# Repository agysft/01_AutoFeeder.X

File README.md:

# AutoFeeder

This is a test project for an auto-feeder for CompactPnP. When the switch is pressed, the feeder moves one frame. It includes a program and a schematic. The program was written in PIC MPLAB X IDE. The schematic is written in KiCAD and the printed circuit board is made. The structure was made with a 3D printer.

---
これはCompactPnP用のオートフィーダーのテスト用プロジェクトです。スイッチが押されるとフィーダーが一コマ移動します。プログラムと回路図を含みます。プログラムはPIC MPLAB X IDEで書きました。回路図はKiCADで書き、プリント基板を作っています。構造物は3Dプリンターで作りました。

---
### Rev.01
* [demo](image/ezgif.com-video-to-gif-converted.gif)
* [schematics](schematics/AutoFeeder_Drum-type_new/20231123_R1/AutoFeeder_Drum-type.pdf) 
* block chart
```mermaid
graph LR
  A[Timer2]-->B[PWM3]-->C
  subgraph BA6211
  C[FWD]
  E[REV]
  end
  A-->D[PWM4]-->E
  F[Sensor0]-->|-|M[CMP2]-->N[LED Green]
    L[FVR 1.024V]-->|+|M
    L-->|+|Q
  I[Sensor1]-->|-|Q[CMP1]-->K[LED Red]
```
---

### Rev.02
フォトセンサーの感度を切り替える回路と、ドラムの角度を取得するためのAS5600という磁気センサーと、I2CのLCDを接続できるようにしました。Add a circuit to switch the sensitivity of the photo sensor, a magnetic sensor named AS5600 to get the angle of the drum, and the LCD.

* [demo](image/20240212_AutoFeederTest-ezgif.com-video-to-gif-converter.gif)
* [schematics](schematics/AutoFeeder_Drum-type_new/20240107_Rev02/AutoFeeder_Drum-type.pdf) 
* block chart

```mermaid
graph LR
  G[Senror1 Radder detector]--> S
  F[Sensor0 Tape-hole detector]--> S
  S{Switch} -->| M- |M
  subgraph BA6211
  C[FWD]
  E[REV]
  end
  BA6211 --- Z[Motor]
  subgraph PIC16F1705
  A[Timer2 50KHz]-->D
  A-->B
  B[PWM3 -- RC5]---C
  D[PWM4 -- RC4]---E
  L[FVR 2.048V]-->| P+ |M[CMP2 -- RA0]
  RA4[GPIO RA4 Open Drain]
  RA5[GPIO RA5 Open Drain]
  end
  M-->N[LED]
  AS5600---|I2C|PIC16F1705
  PIC16F1705---|I2C|LCD
  
  H[Optical Sensor Sensitivity Selector]---RA4
  H---RA5
```

* High-Endurance Flash memory (HEF) usage 0x1F80-0x1F9F
  | Offset Address | note (1 word = 14-bit wide) |
  |:--:|---- 
  | 25 .. 31 | No Use |
  | 2 .. 24 | Tape hole position data (12-bit wide) |
  | 1 | Tape-Color data (White/Transparent/Black)|
  | 0 | AS5600 Magnetic data of origin (12-bit wide) |
* HEF 0x1FA0-0x1FFF is not use.

---
### AutoFeeder2 Rev.1
Autofeeder Rev.02の機能はそのままに、基板を縦置きする事で省スペース化を図りました。また、透過型のフォトインタラプターCNZ1023を使えるようにしました。The functions of the Autofeeder are retained, but the board is placed vertically to save space. Transmissive photo interrupter CNZ1023 can also be used.

* [demo](image/20240803_AutoFeeder_Test2.gif)
* [schematics](schematics/AutoFeeder_Drum-type_2/20240519_AF2_rev1/AutoFeeder_Drum-type.pdf) 

---
### Tips

* PIC16F1705でI2C を設定する。何故か400kHzに設定するとハングします。「Registers」で SSP1ADD = 0x9 (=400KHz)に設定することは可能。
  
  Setting I2C on the PIC16F1705. It hangs when set to 400kHz. It is possible to set SSP1ADD = 0x9 (=400KHz) in "Registers".

* このI2Cのサンプルコードがよく出来ていてそのままincludeして使える。
  This I2C sample code is well done and can be included and used as is.

* HEF-block範囲にプログラムが書かれないようにする設定。
  Settings to prevent programs from being written in the HEF-block range

* PICに書いた時にHEFブロックが初期化されない設定。
  Settings to prevent the HEF-block from being initialized when writing to the PIC

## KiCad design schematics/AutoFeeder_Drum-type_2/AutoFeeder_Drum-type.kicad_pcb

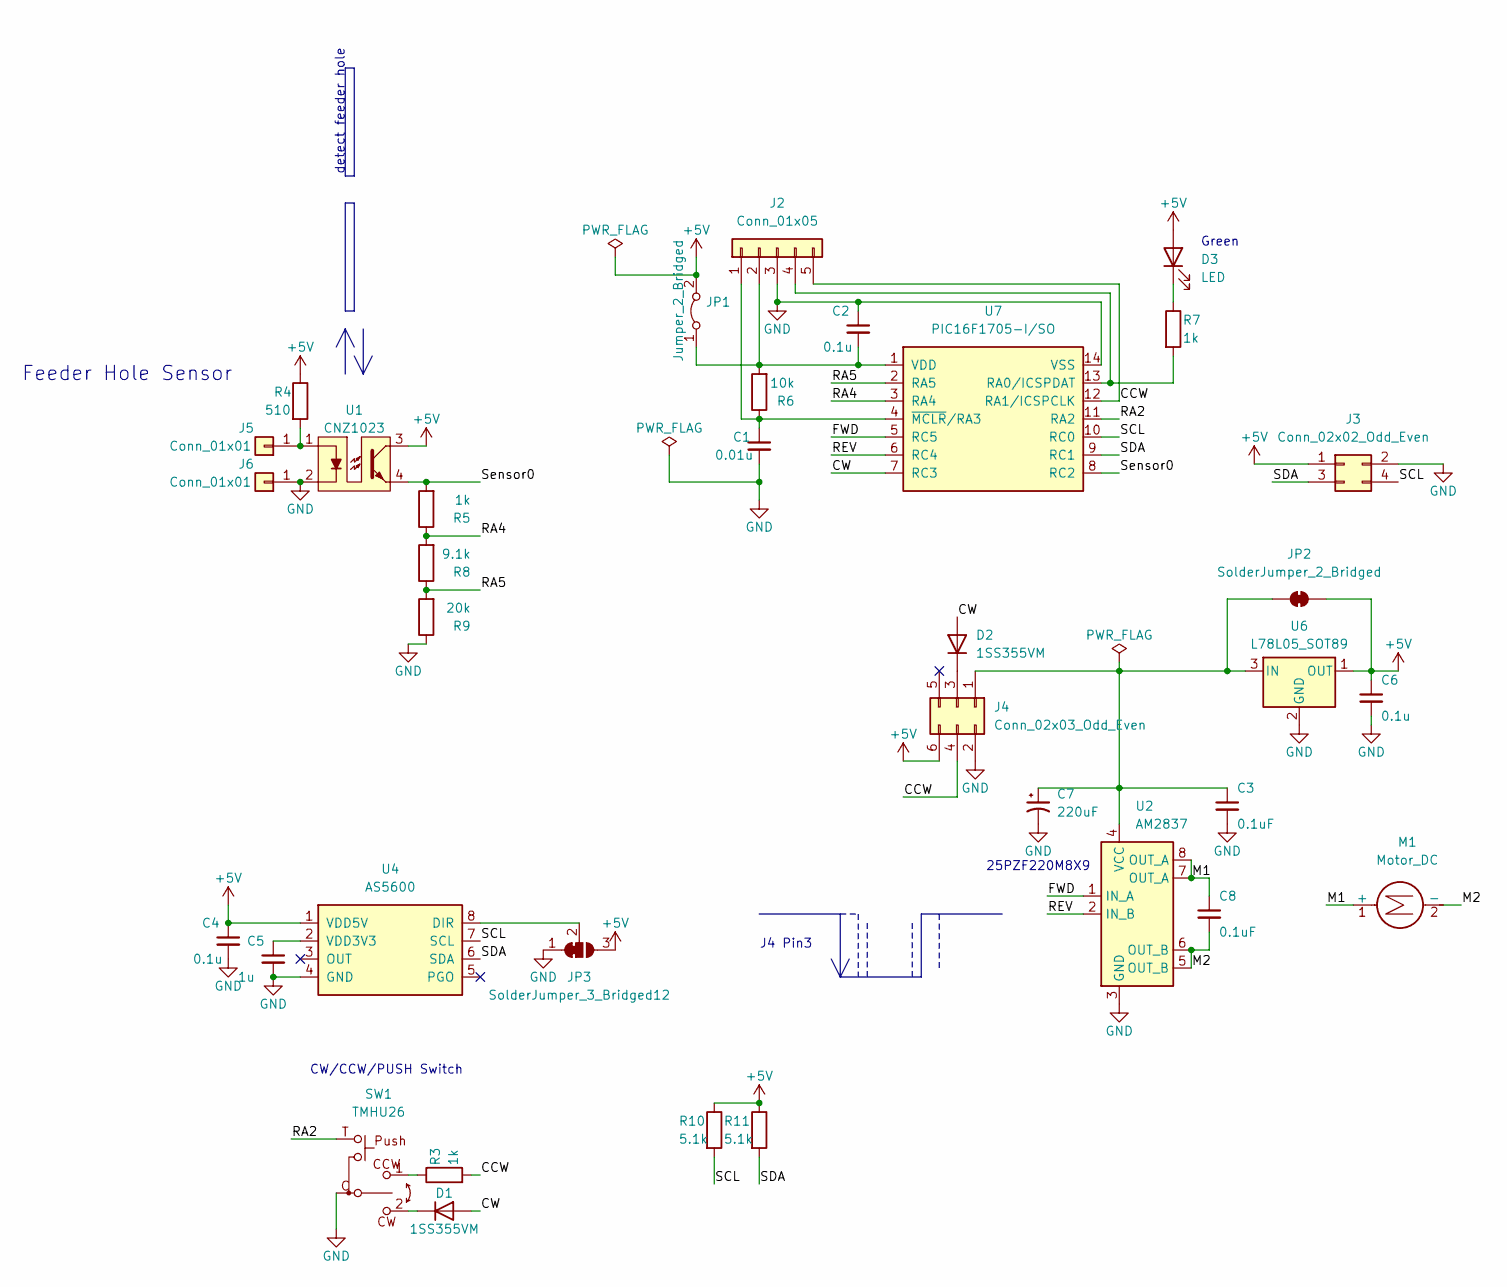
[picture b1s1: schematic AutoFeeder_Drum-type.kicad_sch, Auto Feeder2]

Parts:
C1: 0.01u; C_0603_1608Metric
C2, C4, C6: 0.1u; C_0805_2012Metric
C3, C8: 0.1uF; C_0805_2012Metric
C5: 1u; C_0805_2012Metric
C7: 220uF; CP_Radial_D8.0mm_P3.50mm
D1, D2: 1SS355VM; D_SOD-323F
D3: LED; LED_0603_1608Metric
J2: Conn_01x05; PinHeader_1x05_P2.54mm_Vertical
J3: Conn_02x02_Odd_Even; PinHeader_2x02_P2.54mm_Vertical
J4: Conn_02x03_Odd_Even; PinHeader_2x03_P2.54mm_Vertical
J5, J6: Conn_01x01; PinHeader_1x01_P2.54mm_Vertical
JP1: Jumper_2_Bridged; PinHeader_1x02_P2.54mm_Horizontal
JP2: SolderJumper_2_Bridged; SolderJumper-2_P1.3mm_Bridged_RoundedPad1.0x1.5mm
JP3: SolderJumper_3_Bridged12; SolderJumper-3_P1.3mm_Bridged12_RoundedPad1.0x1.5mm
M1: Motor_DC; JST_XH_B2B-XH-A_1x02_P2.50mm_Vertical
R3, R5, R7: 1k; R_0603_1608Metric
R4: 510; R_0603_1608Metric
R6: 10k; R_0603_1608Metric
R8: 9.1k; R_0603_1608Metric
R9: 20k; R_0603_1608Metric
R10, R11: 5.1k; R_0603_1608Metric
SW1: TMHU26; THMU26_2
U1: CNZ1023
U2: AM2837; SOIC-8_3.9x4.9mm_P1.27mm
U4: AS5600; SOP-8_3.9x4.9mm_P1.27mm
U6: L78L05_SOT89; SOT-89-3
U7: PIC16F1705-I/SO; SOIC-14_3.9x8.7mm_P1.27mm

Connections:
+5V: C4.1, C6.1, D3.2 (A), J3.1, J4.6, JP1.2 (B), JP2.2 (B), JP3.3 (B), R4.1, R10.1, R11.1, U1.3, U4.1 (VDD5V), U6.1 (OUT)
/CCW: J2.5, J4.4, R3.2, U7.12 (RA1/ICSPCLK)
/CW: D1.2 (A), D2.2 (A), U7.7 (RC3)
/FWD: U2.1 (IN_A), U7.5 (RC5)
/M1: C8.1, M1.1 (+), U2.7 (OUT_A), U2.8 (OUT_A)
/M2: C8.2, M1.2 (-), U2.5 (OUT_B), U2.6 (OUT_B)
/RA2: SW1.T, U7.11 (RA2)
/RA4: R5.1, R8.2, U7.3 (RA4)
/RA5: R8.1, R9.2, U7.2 (RA5)
/REV: U2.2 (IN_B), U7.6 (RC4)
/SCL: J3.4, R10.2, U4.7 (SCL), U7.10 (RC0)
/SDA: J3.3, R11.2, U4.6 (SDA), U7.9 (RC1)
/Sensor0: R5.2, U1.4, U7.8 (RC2)
GND: C1.2, C2.1, C3.2, C4.2, C5.2, C6.2, C7.2, J2.3, J3.2, J4.2, J6.1, JP3.1 (A), R9.1, SW1.C, U1.2, U2.3 (GND), U4.4 (GND), U6.2 (GND), U7.14 (VSS)
unnamed: D1.1 (K), SW1.2
unnamed: D2.1 (K), J4.3
unnamed: D3.1 (K), R7.1
unnamed: C1.1, J2.1, R6.1, U7.4 (~MCLR/RA3)
unnamed: C2.2, J2.2, JP1.1 (A), R6.2, U7.1 (VDD)
unnamed: J2.4, R7.2, U7.13 (RA0/ICSPDAT)
unnamed: C3.1, C7.1, J4.1, JP2.1 (A), U2.4 (VCC), U6.3 (IN)
unnamed: J5.1, R4.2, U1.1
unnamed: JP3.2 (C), U4.8 (DIR)
unnamed: R3.1, SW1.1
unnamed: C5.1, U4.2 (VDD3V3)

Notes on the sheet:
J4 Pin3
Green
detect feeder hole
CW/CCW/PUSH Switch
Feeder Hole Sensor
25PZF220M8X9

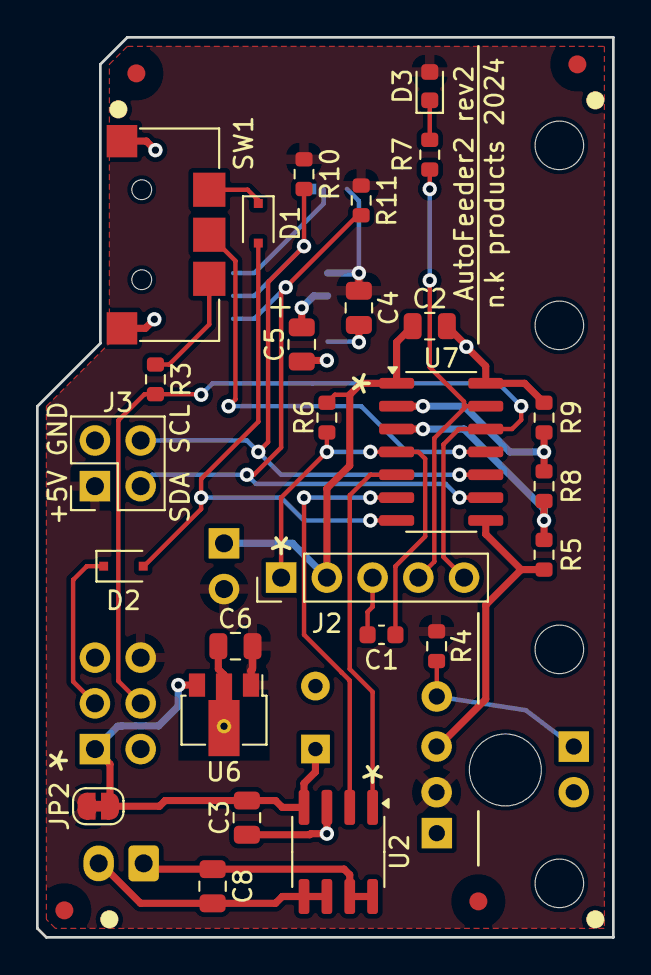
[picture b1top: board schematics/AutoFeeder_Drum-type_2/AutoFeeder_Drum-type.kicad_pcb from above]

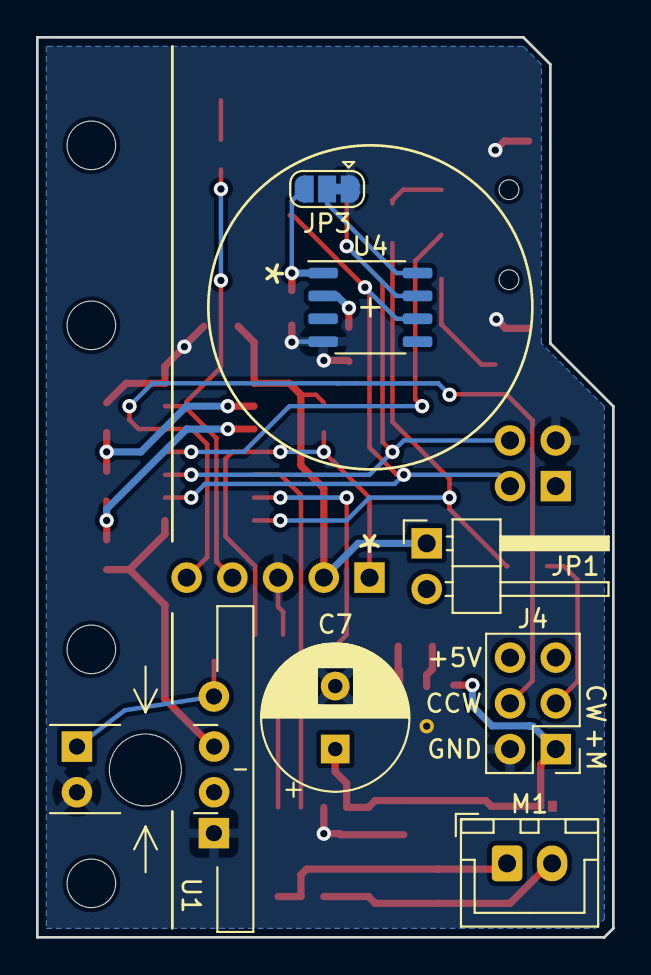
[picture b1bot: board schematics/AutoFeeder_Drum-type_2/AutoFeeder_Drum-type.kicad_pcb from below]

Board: 2 copper layers, 32.0 x 50.0 mm, 43 parts (9 on the bottom side), 25 nets.

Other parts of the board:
Fed1, Fed2, Fed3: Fiducial_1mm_Mask3mm
Fid4: Fiducial_1mm_Mask3mm
Fid5, Fid6, Fid7, Fid8: Fiducial_Silk

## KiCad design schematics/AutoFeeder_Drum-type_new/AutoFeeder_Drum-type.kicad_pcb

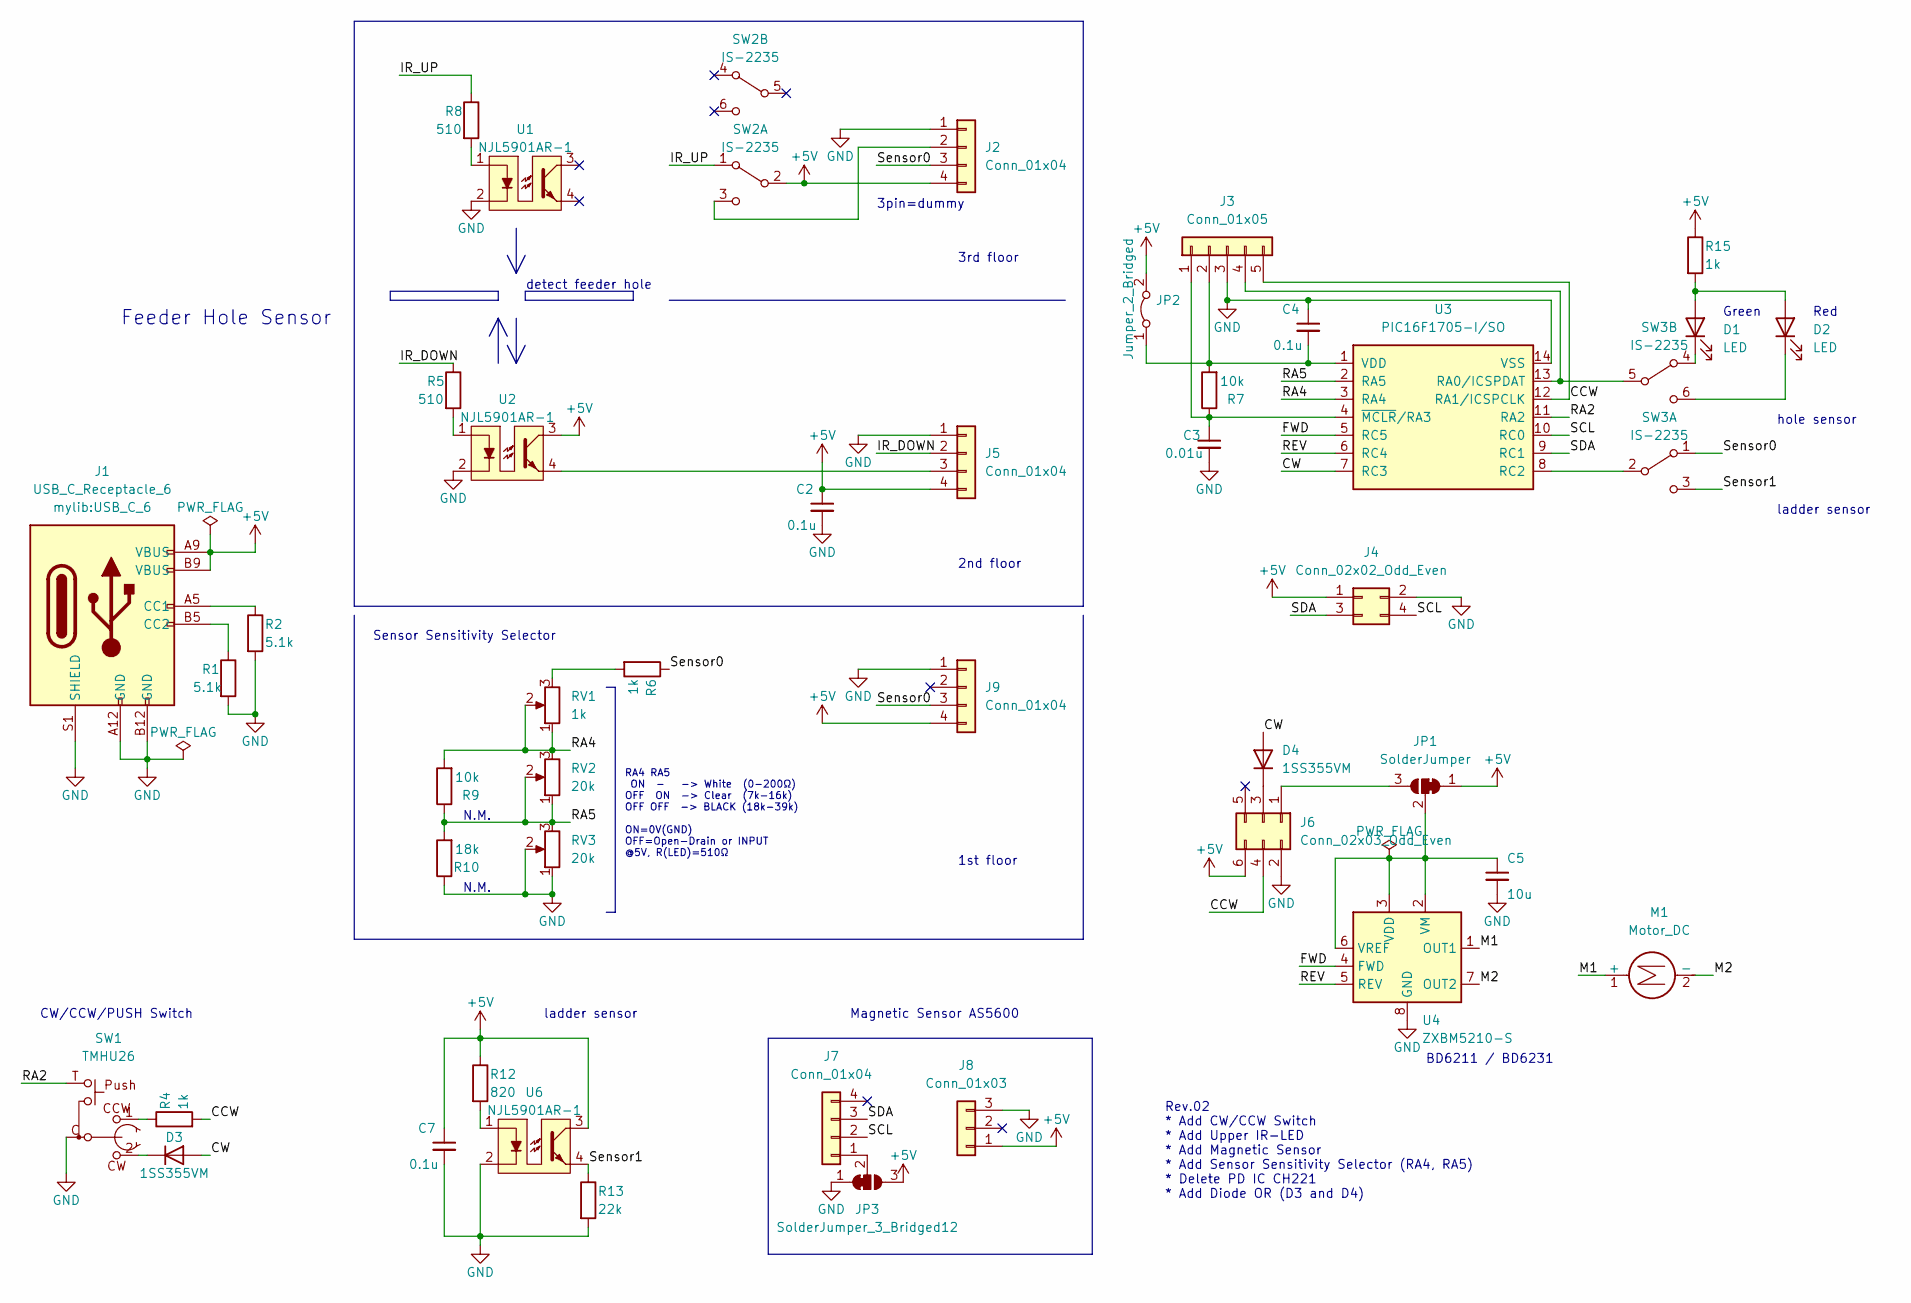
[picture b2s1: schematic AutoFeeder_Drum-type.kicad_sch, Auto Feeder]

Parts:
C2, C4, C7: 0.1u; C_0603_1608Metric
C3: 0.01u; C_0603_1608Metric
C5: 10u; C_0805_2012Metric
D1, D2: LED; LED_0603_1608Metric
D3, D4: 1SS355VM; D_SOD-323F
J1: USB_C_Receptacle_6; USB_C_6
J2, J5, J7, J9: Conn_01x04; PinHeader_1x04_P2.54mm_Vertical
J3: Conn_01x05; PinHeader_1x05_P2.54mm_Vertical
J4: Conn_02x02_Odd_Even; PinHeader_2x02_P2.54mm_Vertical
J6: Conn_02x03_Odd_Even; PinHeader_2x03_P2.54mm_Vertical
J8: Conn_01x03; PinHeader_1x03_P2.54mm_Vertical
JP1: SolderJumper; SolderJumper-3_P1.3mm_Bridged12_RoundedPad1.0x1.5mm
JP2: Jumper_2_Bridged; PinHeader_2x01_P2.54mm_Vertical
JP3: SolderJumper_3_Bridged12; SolderJumper-3_P1.3mm_Bridged12_RoundedPad1.0x1.5mm
M1: Motor_DC; JST_XH_B2B-XH-A_1x02_P2.50mm_Vertical
R1, R2: 5.1k; R_0603_1608Metric
R4, R6, R15: 1k; R_0603_1608Metric
R5, R8: 510; R_0603_1608Metric
R7, R9: 10k; R_0603_1608Metric
R10: 18k; R_0603_1608Metric
R12: 820; R_0603_1608Metric
R13: 22k; R_0603_1608Metric
RV1: 1k; Potentiometer_Vishay_T73YP_Vertical
RV2, RV3: 20k; Potentiometer_Vishay_T73YP_Vertical
SW1: TMHU26; THMU26_2
SW2, SW3: IS-2235; Slide-SW-IS-2235
U1, U2, U6: NJL5901AR-1
U3: PIC16F1705-I/SO; SOIC-14_3.9x8.7mm_P1.27mm
U4: ZXBM5210-S; SOIC-8_3.9x4.9mm_P1.27mm

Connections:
+5V: C2.1, C7.1, J1.A9 (VBUS), J1.B9 (VBUS), J2.4, J4.1, J5.4, J6.6, J8.1, J9.4, JP1.1 (A), JP2.2 (B), JP3.3 (B), R12.1, R15.1, SW2.2 (B), U2.3, U6.3
/CCW: J3.5, J6.4, R4.2, U3.12 (RA1/ICSPCLK)
/CW: D3.2 (A), D4.2 (A), U3.7 (RC3)
/FWD: U3.5 (RC5), U4.4 (FWD)
/IR_DOWN: J5.2, R5.1
/IR_UP: R8.1, SW2.1 (A)
/M1: M1.1 (+), U4.1 (OUT1)
/M2: M1.2 (-), U4.7 (OUT2)
/RA2: SW1.T, U3.11 (RA2)
/RA4: R9.2, RV1.1, RV1.2, RV2.3, U3.3 (RA4)
/RA5: R9.1, R10.2, RV2.1, RV2.2, RV3.3, U3.2 (RA5)
/REV: U3.6 (RC4), U4.5 (REV)
/SCL: J4.4, J7.2, U3.10 (RC0)
/SDA: J4.3, J7.3, U3.9 (RC1)
/Sensor0: J2.3, J9.3, R6.1, SW3.1 (A)
/Sensor1: R13.1, SW3.3 (C), U6.4
GND: C2.2, C3.2, C4.1, C5.2, C7.2, J1.A12 (GND), J1.B12 (GND), J1.S1 (SHIELD), J2.1, J3.3, J4.2, J5.1, J6.2, J8.3, J9.1, JP3.1 (A), R1.2, R2.2, R10.1, R13.2, RV3.1, RV3.2, SW1.C, U1.2, U2.2, U3.14 (VSS), U4.8 (GND), U6.2
unnamed: C3.1, J3.1, R7.1, U3.4 (~MCLR/RA3)
unnamed: C4.2, J3.2, JP2.1 (A), R7.2, U3.1 (VDD)
unnamed: C5.1, JP1.2 (C), U4.2 (VM), U4.3 (VDD), U4.6 (VREF)
unnamed: D1.1 (K), SW3.4 (A)
unnamed: D1.2 (A), D2.2 (A), R15.2
unnamed: D2.1 (K), SW3.6 (C)
unnamed: D3.1 (K), SW1.2
unnamed: D4.1 (K), J6.3
unnamed: J1.A5 (CC1), R2.1
unnamed: J1.B5 (CC2), R1.1
unnamed: J2.2, SW2.3 (C)
unnamed: J3.4, SW3.5 (B), U3.13 (RA0/ICSPDAT)
unnamed: J5.3, U2.4
unnamed: J6.1, JP1.3 (B)
unnamed: J7.1, JP3.2 (C)
unnamed: R4.1, SW1.1
unnamed: R5.2, U2.1
unnamed: R6.2, RV1.3
unnamed: R8.2, U1.1
unnamed: R12.2, U6.1
unnamed: SW3.2 (B), U3.8 (RC2)

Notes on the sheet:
Green
detect feeder hole
1st floor
RA4 RA5 ON - -> White (0-200Ω) OFF ON -> Clear (7k-16k) OFF OFF -> BLACK (18k-39k) ON=0V(GND) OFF=Open-Drain or INPUT @5V, R(LED)=510Ω
3pin=dummy
BD6211 / BD6231
2nd floor
ladder sensor
Red
N.M.
CW/CCW/PUSH Switch
Feeder Hole Sensor
Magnetic Sensor AS5600
hole sensor
Rev.02 * Add CW/CCW Switch * Add Upper IR-LED * Add Magnetic Sensor * Add Sensor Sensitivity Selector (RA4, RA5) * Delete PD IC CH221 * Add Diode OR (D3 and D4)
Sensor Sensitivity Selector
3rd floor

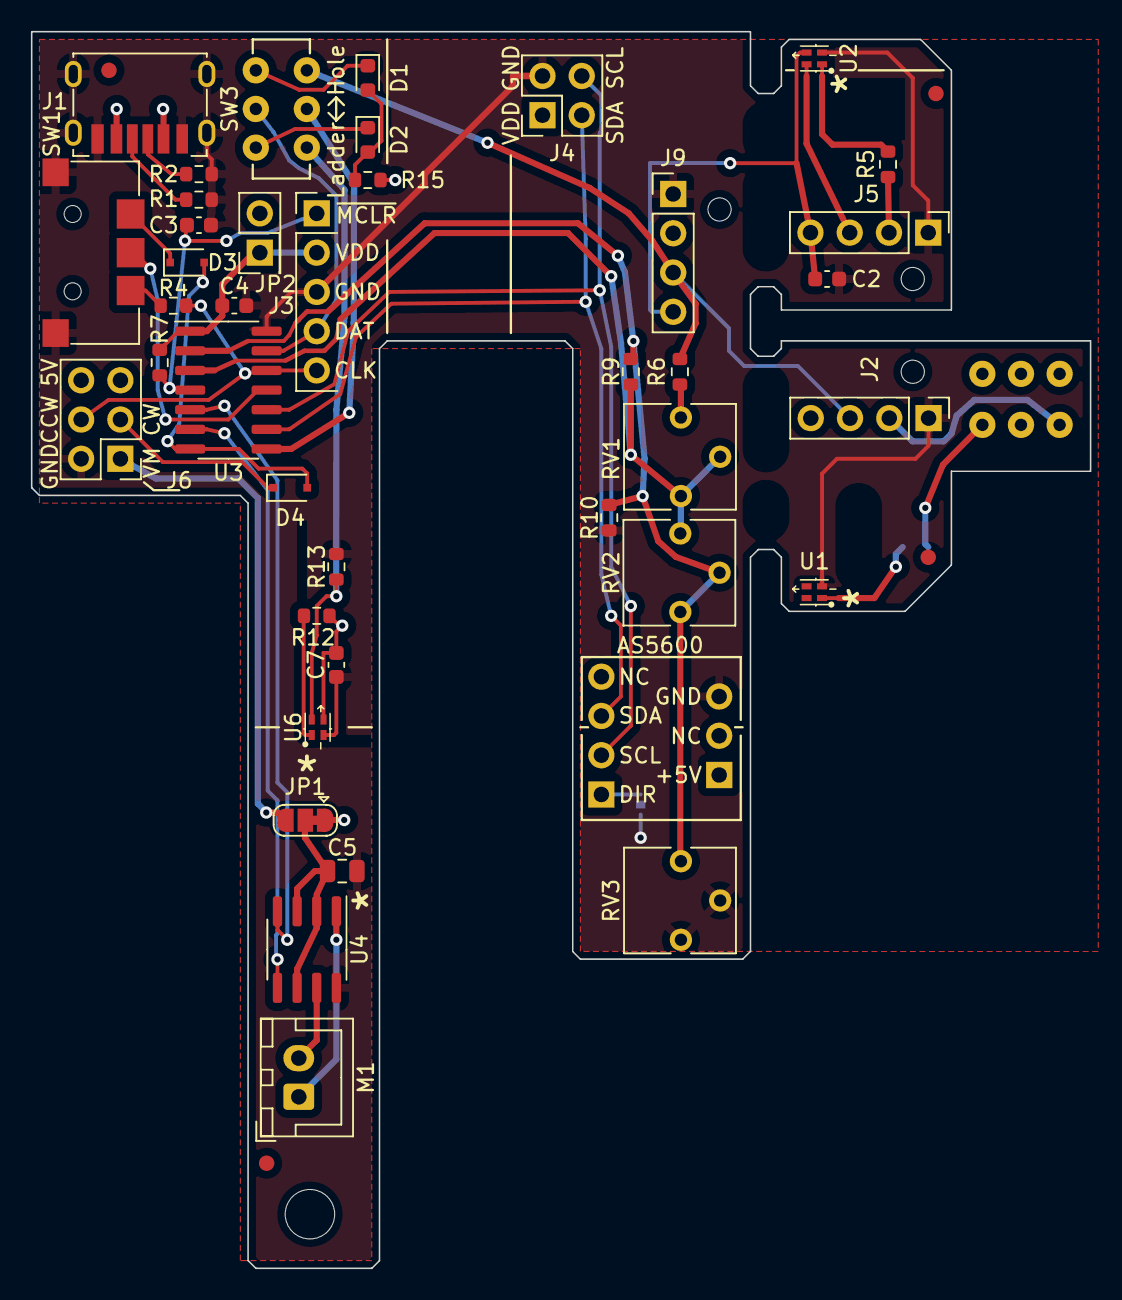
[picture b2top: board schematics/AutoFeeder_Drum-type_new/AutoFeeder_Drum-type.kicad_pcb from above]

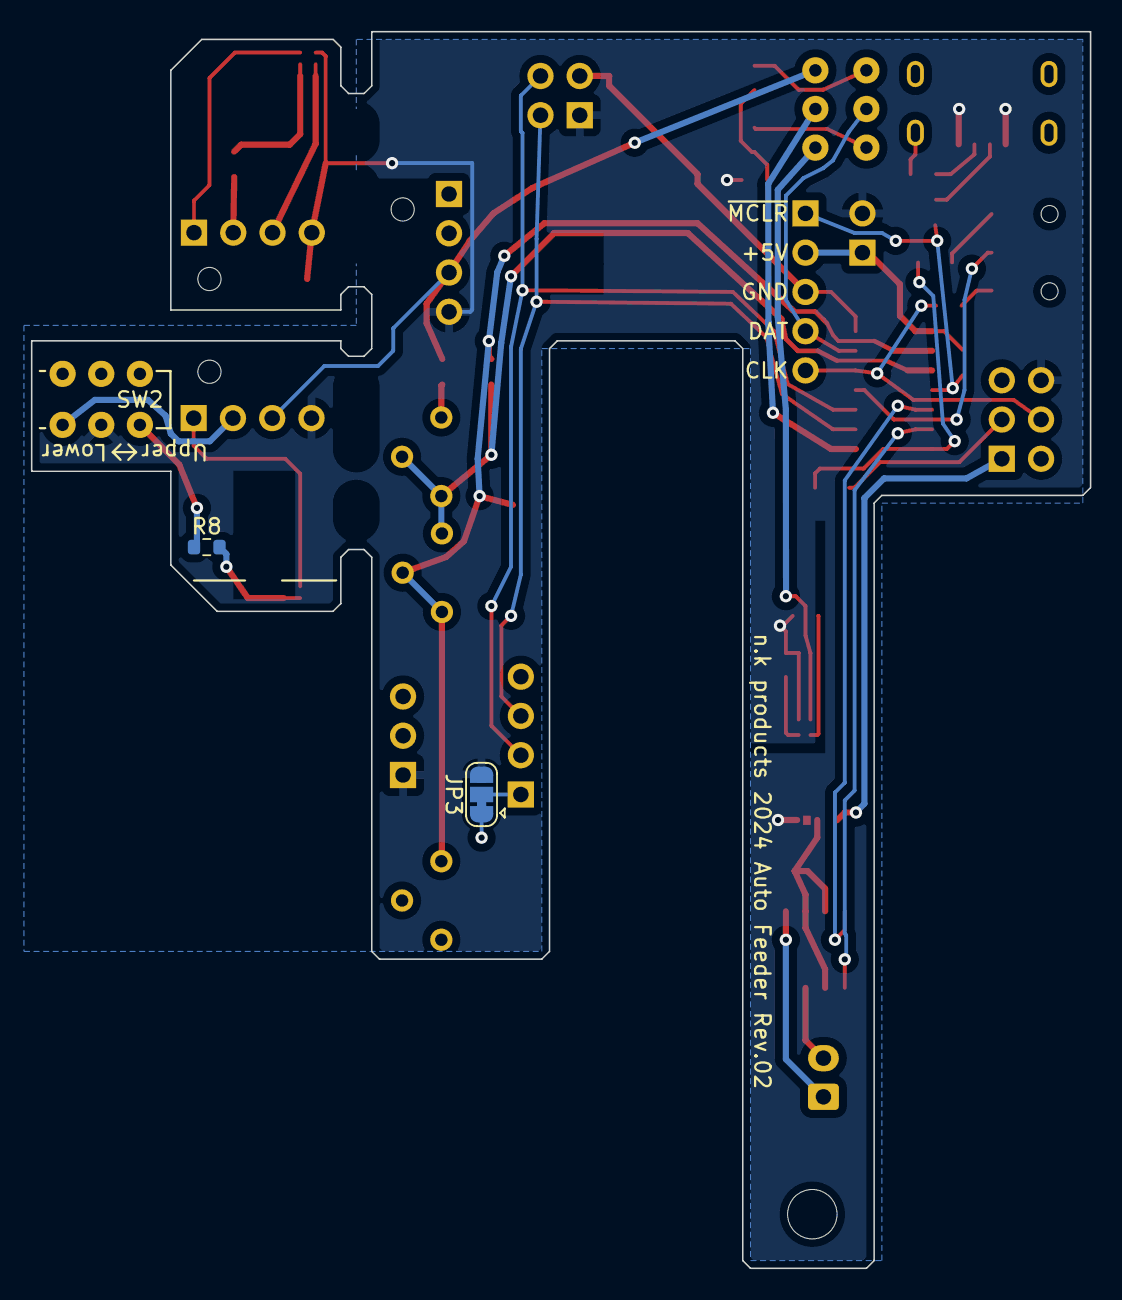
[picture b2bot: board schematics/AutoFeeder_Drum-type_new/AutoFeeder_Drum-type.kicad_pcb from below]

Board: 2 copper layers, 68.5 x 80.0 mm, 45 parts (3 on the bottom side), 38 nets.

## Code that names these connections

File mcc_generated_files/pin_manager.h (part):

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#define RA0_SetHigh()            do { LATAbits.LATA0 = 1; } while(0)
#define RA0_SetLow()             do { LATAbits.LATA0 = 0; } while(0)
#define RA0_Toggle()             do { LATAbits.LATA0 = ~LATAbits.LATA0; } while(0)
#define RA0_GetValue()              PORTAbits.RA0
#define RA0_SetDigitalInput()    do { TRISAbits.TRISA0 = 1; } while(0)
#define RA0_SetDigitalOutput()   do { TRISAbits.TRISA0 = 0; } while(0)
#define RA0_SetPullup()             do { WPUAbits.WPUA0 = 1; } while(0)
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// get/set IO_RA1 aliases
#define IO_RA1_TRIS                 TRISAbits.TRISA1
#define IO_RA1_LAT                  LATAbits.LATA1
#define IO_RA1_PORT                 PORTAbits.RA1
#define IO_RA1_WPU                  WPUAbits.WPUA1
#define IO_RA1_OD                   ODCONAbits.ODA1
#define IO_RA1_ANS                  ANSELAbits.ANSA1
#define IO_RA1_SetHigh()            do { LATAbits.LATA1 = 1; } while(0)
#define IO_RA1_SetLow()             do { LATAbits.LATA1 = 0; } while(0)
#define IO_RA1_Toggle()             do { LATAbits.LATA1 = ~LATAbits.LATA1; } while(0)
#define IO_RA1_GetValue()           PORTAbits.RA1
#define IO_RA1_SetDigitalInput()    do { TRISAbits.TRISA1 = 1; } while(0)
#define IO_RA1_SetDigitalOutput()   do { TRISAbits.TRISA1 = 0; } while(0)
#define IO_RA1_SetPullup()          do { WPUAbits.WPUA1 = 1; } while(0)
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// get/set IO_RA2 aliases
#define IO_RA2_TRIS                 TRISAbits.TRISA2
#define IO_RA2_LAT                  LATAbits.LATA2
#define IO_RA2_PORT                 PORTAbits.RA2
#define IO_RA2_WPU                  WPUAbits.WPUA2
#define IO_RA2_OD                   ODCONAbits.ODA2
#define IO_RA2_ANS                  ANSELAbits.ANSA2
#define IO_RA2_SetHigh()            do { LATAbits.LATA2 = 1; } while(0)
#define IO_RA2_SetLow()             do { LATAbits.LATA2 = 0; } while(0)
#define IO_RA2_Toggle()             do { LATAbits.LATA2 = ~LATAbits.LATA2; } while(0)
#define IO_RA2_GetValue()           PORTAbits.RA2
#define IO_RA2_SetDigitalInput()    do { TRISAbits.TRISA2 = 1; } while(0)
#define IO_RA2_SetDigitalOutput()   do { TRISAbits.TRISA2 = 0; } while(0)
#define IO_RA2_SetPullup()          do { WPUAbits.WPUA2 = 1; } while(0)
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// get/set IO_RA4 aliases
#define IO_RA4_TRIS                 TRISAbits.TRISA4
#define IO_RA4_LAT                  LATAbits.LATA4
#define IO_RA4_PORT                 PORTAbits.RA4
#define IO_RA4_WPU                  WPUAbits.WPUA4
#define IO_RA4_OD                   ODCONAbits.ODA4
#define IO_RA4_ANS                  ANSELAbits.ANSA4
#define IO_RA4_SetHigh()            do { LATAbits.LATA4 = 1; } while(0)
#define IO_RA4_SetLow()             do { LATAbits.LATA4 = 0; } while(0)
#define IO_RA4_Toggle()             do { LATAbits.LATA4 = ~LATAbits.LATA4; } while(0)
#define IO_RA4_GetValue()           PORTAbits.RA4
#define IO_RA4_SetDigitalInput()    do { TRISAbits.TRISA4 = 1; } while(0)
#define IO_RA4_SetDigitalOutput()   do { TRISAbits.TRISA4 = 0; } while(0)
#define IO_RA4_SetPullup()          do { WPUAbits.WPUA4 = 1; } while(0)
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// get/set IO_RA5 aliases
#define IO_RA5_TRIS                 TRISAbits.TRISA5
#define IO_RA5_LAT                  LATAbits.LATA5
#define IO_RA5_PORT                 PORTAbits.RA5
#define IO_RA5_WPU                  WPUAbits.WPUA5
#define IO_RA5_OD                   ODCONAbits.ODA5
#define IO_RA5_SetHigh()            do { LATAbits.LATA5 = 1; } while(0)
#define IO_RA5_SetLow()             do { LATAbits.LATA5 = 0; } while(0)
#define IO_RA5_Toggle()             do { LATAbits.LATA5 = ~LATAbits.LATA5; } while(0)
#define IO_RA5_GetValue()           PORTAbits.RA5
#define IO_RA5_SetDigitalInput()    do { TRISAbits.TRISA5 = 1; } while(0)
#define IO_RA5_SetDigitalOutput()   do { TRISAbits.TRISA5 = 0; } while(0)
#define IO_RA5_SetPullup()          do { WPUAbits.WPUA5 = 1; } while(0)
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#define RC0_SetHigh()            do { LATCbits.LATC0 = 1; } while(0)
#define RC0_SetLow()             do { LATCbits.LATC0 = 0; } while(0)
#define RC0_Toggle()             do { LATCbits.LATC0 = ~LATCbits.LATC0; } while(0)
#define RC0_GetValue()              PORTCbits.RC0
#define RC0_SetDigitalInput()    do { TRISCbits.TRISC0 = 1; } while(0)
#define RC0_SetDigitalOutput()   do { TRISCbits.TRISC0 = 0; } while(0)
#define RC0_SetPullup()             do { WPUCbits.WPUC0 = 1; } while(0)
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#define RC1_SetHigh()            do { LATCbits.LATC1 = 1; } while(0)
#define RC1_SetLow()             do { LATCbits.LATC1 = 0; } while(0)
#define RC1_Toggle()             do { LATCbits.LATC1 = ~LATCbits.LATC1; } while(0)
#define RC1_GetValue()              PORTCbits.RC1
#define RC1_SetDigitalInput()    do { TRISCbits.TRISC1 = 1; } while(0)
#define RC1_SetDigitalOutput()   do { TRISCbits.TRISC1 = 0; } while(0)
#define RC1_SetPullup()             do { WPUCbits.WPUC1 = 1; } while(0)
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#define RC2_SetHigh()            do { LATCbits.LATC2 = 1; } while(0)
#define RC2_SetLow()             do { LATCbits.LATC2 = 0; } while(0)
#define RC2_Toggle()             do { LATCbits.LATC2 = ~LATCbits.LATC2; } while(0)
#define RC2_GetValue()              PORTCbits.RC2
#define RC2_SetDigitalInput()    do { TRISCbits.TRISC2 = 1; } while(0)
#define RC2_SetDigitalOutput()   do { TRISCbits.TRISC2 = 0; } while(0)
#define RC2_SetPullup()             do { WPUCbits.WPUC2 = 1; } while(0)
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// get/set IO_RC3 aliases
#define IO_RC3_TRIS                 TRISCbits.TRISC3
#define IO_RC3_LAT                  LATCbits.LATC3
#define IO_RC3_PORT                 PORTCbits.RC3
#define IO_RC3_WPU                  WPUCbits.WPUC3
#define IO_RC3_OD                   ODCONCbits.ODC3
#define IO_RC3_ANS                  ANSELCbits.ANSC3
#define IO_RC3_SetHigh()            do { LATCbits.LATC3 = 1; } while(0)
#define IO_RC3_SetLow()             do { LATCbits.LATC3 = 0; } while(0)
#define IO_RC3_Toggle()             do { LATCbits.LATC3 = ~LATCbits.LATC3; } while(0)
#define IO_RC3_GetValue()           PORTCbits.RC3
#define IO_RC3_SetDigitalInput()    do { TRISCbits.TRISC3 = 1; } while(0)
#define IO_RC3_SetDigitalOutput()   do { TRISCbits.TRISC3 = 0; } while(0)
#define IO_RC3_SetPullup()          do { WPUCbits.WPUC3 = 1; } while(0)
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#define RC4_SetHigh()            do { LATCbits.LATC4 = 1; } while(0)
#define RC4_SetLow()             do { LATCbits.LATC4 = 0; } while(0)
#define RC4_Toggle()             do { LATCbits.LATC4 = ~LATCbits.LATC4; } while(0)
#define RC4_GetValue()              PORTCbits.RC4
#define RC4_SetDigitalInput()    do { TRISCbits.TRISC4 = 1; } while(0)
#define RC4_SetDigitalOutput()   do { TRISCbits.TRISC4 = 0; } while(0)
#define RC4_SetPullup()             do { WPUCbits.WPUC4 = 1; } while(0)
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#define RC5_SetHigh()            do { LATCbits.LATC5 = 1; } while(0)
#define RC5_SetLow()             do { LATCbits.LATC5 = 0; } while(0)
#define RC5_Toggle()             do { LATCbits.LATC5 = ~LATCbits.LATC5; } while(0)
#define RC5_GetValue()              PORTCbits.RC5
#define RC5_SetDigitalInput()    do { TRISCbits.TRISC5 = 1; } while(0)
#define RC5_SetDigitalOutput()   do { TRISCbits.TRISC5 = 0; } while(0)
#define RC5_SetPullup()             do { WPUCbits.WPUC5 = 1; } while(0)
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
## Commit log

2023-12-18 1st commit
2023-12-19 Add an image and the schematics.
2023-12-19 Change mp4-->gif
2023-12-19 Add block chart
2023-12-20 Add overview image
2023-12-20 Edit readme.md
2023-12-29 Program: Add I2C function; Add LCD; Add Magnetic sensor; Schematics: Add KiCAD files
2023-12-30 Modified main.c for easier viewing. Change X IDE version 6.00 --> 6.15; Update the MCC version;
2023-12-30 Tried non-volatile memory (High-Endurance FLASH MEMORY). http://ww1.microchip.com/downloads/en/appnotes/00001673a.pdf XC8 has been updated and the manner in which inline assemblers are written has ch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
2023-12-31 Test reading/writing from/to HEF-block
2024-01-07 Rev.02: Rev01 had a problem with the deep feeder hitting the PCB. Rev02 avoided this problem by overlapping two PCBs for the sensor section.; Three sensitivity options are available for white, transp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
2024-01-08 Change Schematics; Add Red LED for ladder sensor; Add guide line of feeder tape
2024-01-08 PCB modification: Slightly lengthened the pins of the USB Type-C connector to improve solderability.
2024-01-08 Change schematics: Assign CW/CCW pin to connector; Add M3 mounting hole
2024-01-08 Schematics: Add +5V to J6; Fine-tuning of patterns
2024-01-09 Schematics: Add Diode OR (D3 and D4) for manual feed and auto feed
2024-01-16 Change the position of M3 mounting hole / Add silk printing of magnetic sensor / Add Diode OR (D3,D4) to allow advancing one component either by manual switch or automatic control / Slightly modified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
2024-02-12 Support Rev.02 PCB.
2024-02-18 Auto Select the Tape Color; Add Rev02 demo; Edit Readme;
2024-02-18 When the power is turned on, rotate in the direction closest to the distance of the stored magnetic sensor value.
2024-02-18 Edit README
2024-02-23 Made code easier to read; Subroutines, comments, etc.; Add Open-PnP files
2024-03-03 Add a circuit to switch the sensitivity of the photo sensor, a magnetic sensor named AS5600 to get the angle of the drum, and the LCD.
2024-03-11 Improve accuracy when rewinding; When rewinding, pass the target once and then approach.
2024-04-27 An IOC interrupt was used to detect the falling edge of the CW switch; two timers Timer4/Timer6 were used to eliminate the chatter that occurs on the falling and rising edges of the CW switch. These 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
2024-05-04 Changed to a method that does not use interrupts to remove chatter.
2024-07-28 AutoFeeder_Drum-type_new --> AutoFeeder_Drum-type_2 : Change a board that was placed horizontally to vertically.
2024-08-12 Two types of sensors CNZ1023 and NJL5901 are supported. When the center button is pressed and held for 2 seconds, the hole position is memorized for one revolution, then returns to the original posit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
2024-08-20 Auto Feeder 2 rev.1 ; The board is placed vertically to save space. Transmissive photo interrupter CNZ1023 can also be used.
2024-08-20 Update readme AutoFeeder2 rev01
2024-08-21 Add AF2 rev1 movie

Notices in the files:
mcc_generated_files/pin_manager.h:
(c) 2018 Microchip Technology Inc. and its subsidiaries.
